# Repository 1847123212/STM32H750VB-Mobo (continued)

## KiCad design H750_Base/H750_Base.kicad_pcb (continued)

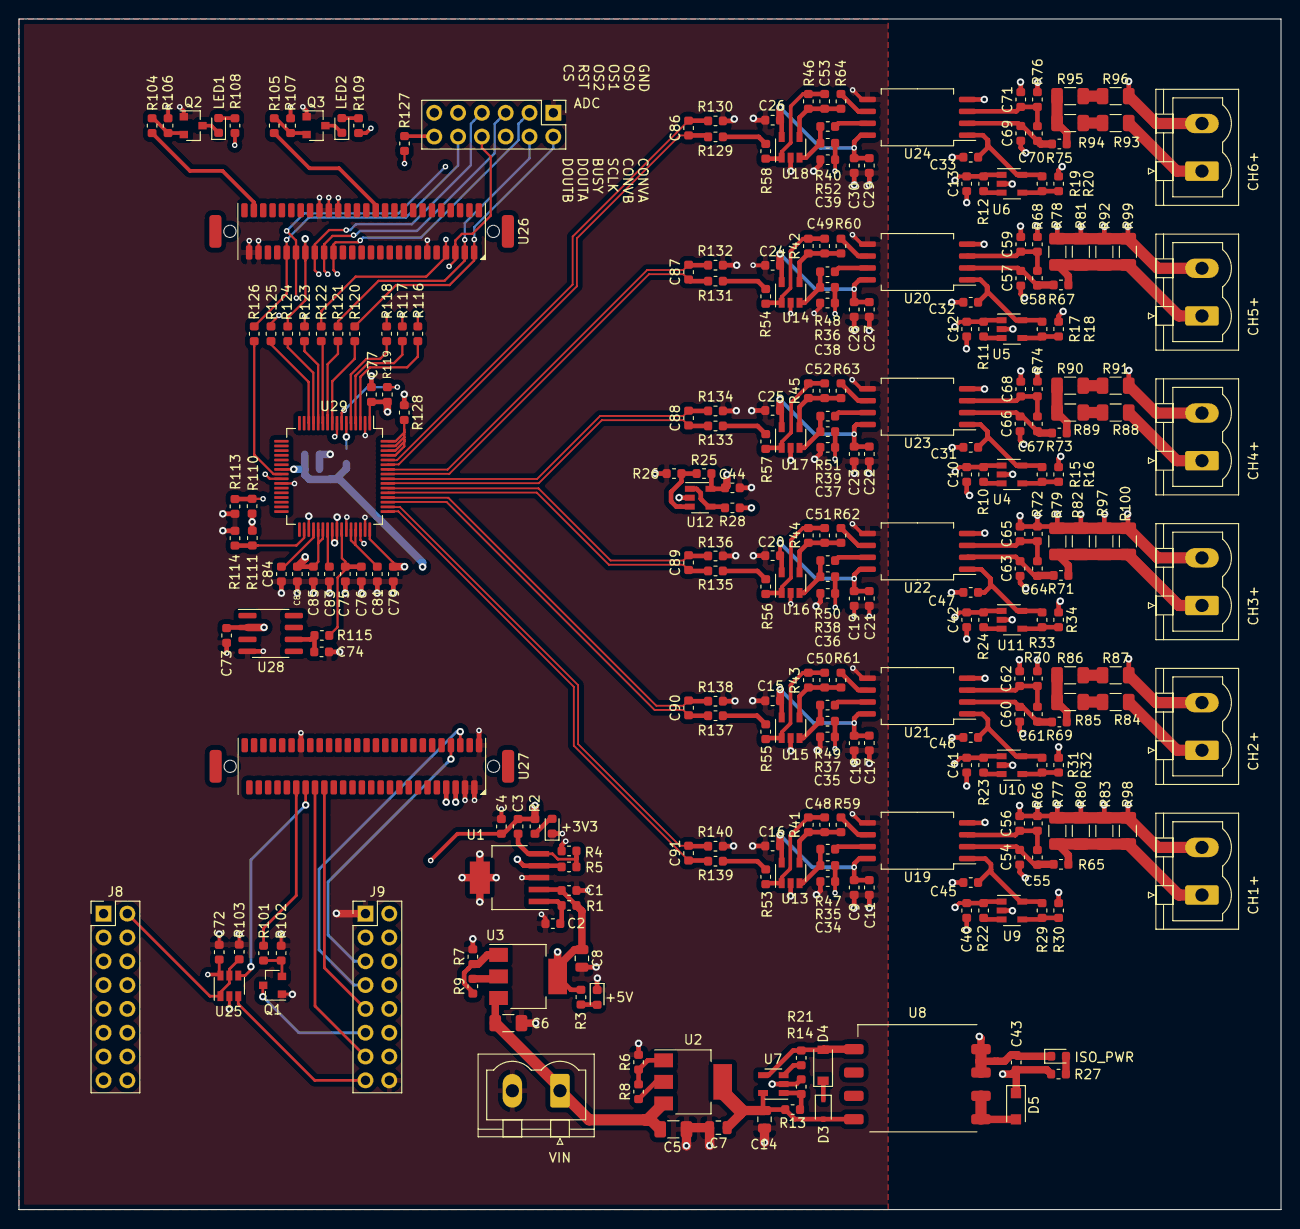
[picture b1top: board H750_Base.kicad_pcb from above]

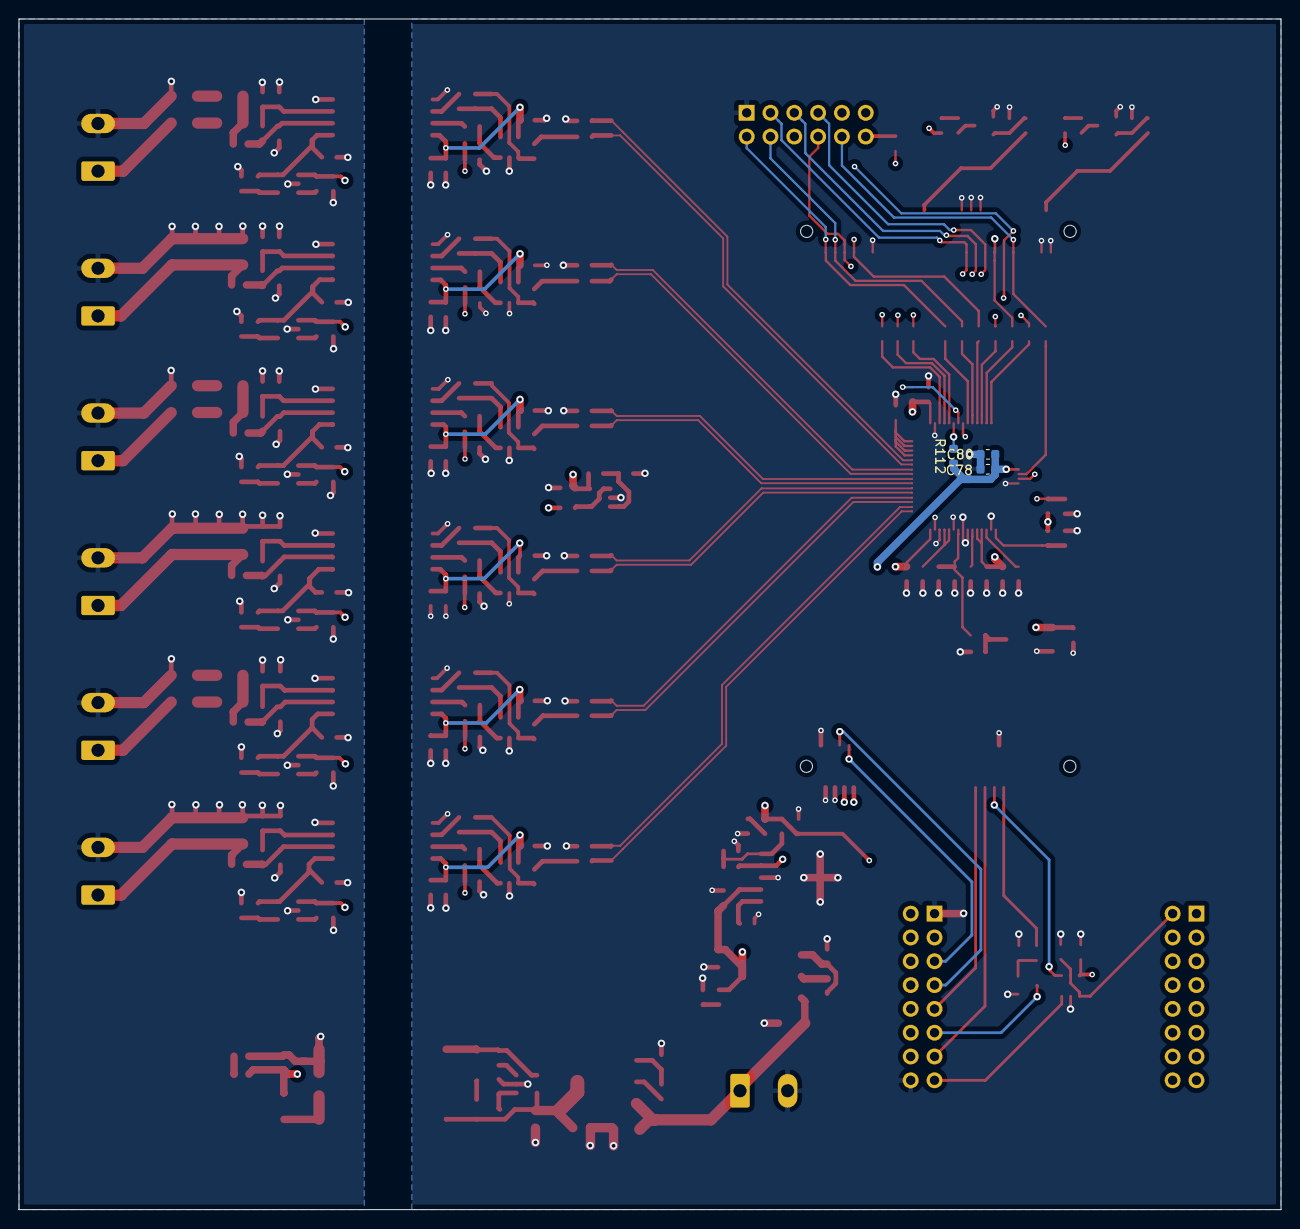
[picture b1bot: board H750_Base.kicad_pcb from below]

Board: 4 copper layers, 134.6 x 127.0 mm, 281 parts (3 on the bottom side), 167 nets.

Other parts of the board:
+3V3: LED_RED; LED_0603_1608Metric
+5V: LED_YELLOW; LED_0603_1608Metric
ADC: AD7606; PinHeader_2x06_P2.54mm_Vertical
CH1+: CH1; PhoenixContact_MSTBVA_2,5_2-G-5,08_1x02_P5.08mm_Vertical
CH2+: CH2; PhoenixContact_MSTBVA_2,5_2-G-5,08_1x02_P5.08mm_Vertical
CH3+: CH3; PhoenixContact_MSTBVA_2,5_2-G-5,08_1x02_P5.08mm_Vertical
CH4+: CH4; PhoenixContact_MSTBVA_2,5_2-G-5,08_1x02_P5.08mm_Vertical
CH5+: CH5; PhoenixContact_MSTBVA_2,5_2-G-5,08_1x02_P5.08mm_Vertical
CH6+: CH6; PhoenixContact_MSTBVA_2,5_2-G-5,08_1x02_P5.08mm_Vertical
ISO_PWR: LED; LED_0603_1608Metric
LED1: USER_LED1; LED_0603_1608Metric
LED2: USER_LED2; LED_0603_1608Metric
VIN: PWR; PhoenixContact_MSTBVA_2,5_2-G-5,08_1x02_P5.08mm_Vertical

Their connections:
/U_ADC/BUSY: ADC.8; also elsewhere on the board
/U_ADC/CONVA: ADC.2; also elsewhere on the board
/U_ADC/CONVB: ADC.4; also elsewhere on the board
/U_ADC/CS: ADC.11; also elsewhere on the board
/U_ADC/DOUTA: ADC.10; also elsewhere on the board
/U_ADC/DOUTB: ADC.12; also elsewhere on the board
/U_ADC/OS0: ADC.3; also elsewhere on the board
/U_ADC/OS1: ADC.5; also elsewhere on the board
/U_ADC/OS2: ADC.7; also elsewhere on the board
/U_Analog/VISO-: CH1+.2, CH2+.2, CH3+.2, CH4+.2, CH5+.2, CH6+.2, ISO_PWR.1; also elsewhere on the board
/U_Connectors/ADRST: ADC.9; also elsewhere on the board
/U_Connectors/SCK: ADC.6; also elsewhere on the board
GND: +3V3.1, +5V.1, ADC.1, VIN.2; also elsewhere on the board
unnamed 87: +3V3.2; also elsewhere on the board
unnamed 88: +5V.2; also elsewhere on the board
unnamed 92: ISO_PWR.2; also elsewhere on the board
unnamed 93: LED1.1; also elsewhere on the board
unnamed 94: LED1.2; also elsewhere on the board
unnamed 95: LED2.1; also elsewhere on the board
unnamed 96: LED2.2; also elsewhere on the board
unnamed 97: CH1+.1; also elsewhere on the board
unnamed 98: CH5+.1; also elsewhere on the board
unnamed 99: CH2+.1; also elsewhere on the board
unnamed 100: CH3+.1; also elsewhere on the board
unnamed 101: CH4+.1; also elsewhere on the board
unnamed 102: CH6+.1; also elsewhere on the board
VIN: VIN.1; also elsewhere on the board

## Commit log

2019-09-08 Ver0.0 PCB design
